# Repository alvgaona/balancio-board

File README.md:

<div align="center">

# balancio-board

**Controller board for the Balancio self-balancing robot.**

</div>

## Overview

The board carries the robot's brains, motor drive and power.

- ESP32 DevKit
- DRV8833 dual motor driver
- MPU-6050 IMU
- 2S battery protection
- Soft-latch power switch, with the power button on the left edge

Rev 1.0 was built by JLCPCB and works. Rev 1.1 replaces its slide switch with the soft latch.

## Layout

- `hw/`: the design, edited in KiCad 10. This is the source of truth.
  - `balancio.kicad_sch`, `balancio.kicad_pcb`: schematic and board.
  - `lib/`: the board's own symbols, footprints and the 3D models KiCad doesn't ship (`balancio.3dshapes/`).
- `scripts/build.sh`: checks the design and writes everything to `build/`.

## Build

You need KiCad 10. FreeCAD is needed only after you edit a model in `hw/lib/balancio.3dshapes/`.

```sh
scripts/build.sh   # or: pixi run build
```

It runs ERC and DRC with schematic parity, and stops on any error before it exports anything.

CI runs the same build in KiCad's Docker image on every push and pull request. The board package is attached to
each run as the `board-package` artifact.

It writes:

- `build/balancio-gerbers.zip`, `build/balancio-bom.csv` and `build/balancio-cpl.csv` for JLCPCB;
- `build/balancio-schematic.pdf`;
- `build/balancio.glb`, the assembled board in 3D, for Blender;
- `build/balancio-rev<rev>.zip`, the board package: all of the above plus the KiCad files, for descent.

## Viewing the board

Open `build/balancio-rev<rev>.zip` in [descent](https://github.com/alvgaona/descent): the 3D model, schematic,
PCB, BOM and every file, in the browser.

descent shows a part as metal when its colour is one of the metals of KiCad's standard 3D models, so our own
models (the DevKit's `.FCStd`) paint metal with those: `#d2d1c7` (metal grey pins) and `#dbbc7e` (gold pins).

`scripts/package.py` writes the package; its docstring describes the format.

## Development

The dev tools (lefthook, commitlint, git-cliff) come from [pixi](https://pixi.sh). Install the git hook once:

```sh
pixi run hooks
```

Commit messages follow [Conventional Commits](https://www.conventionalcommits.org); the `commit-msg` hook checks
them with commitlint.

## Releases

Each board revision is tagged `rev-<rev>`, matching the `rev` in the schematic and PCB title blocks. Pushing the
tag runs the release workflow: it checks the tag against the title blocks, builds the board, and publishes a
GitHub release with the board package, Gerbers, BOM, CPL and schematic PDF. The notes come from git-cliff.
To release a tag that already exists, run the release workflow by hand from the Actions tab and give it the tag.

```sh
pixi run changelog   # write CHANGELOG.md from the commits
```

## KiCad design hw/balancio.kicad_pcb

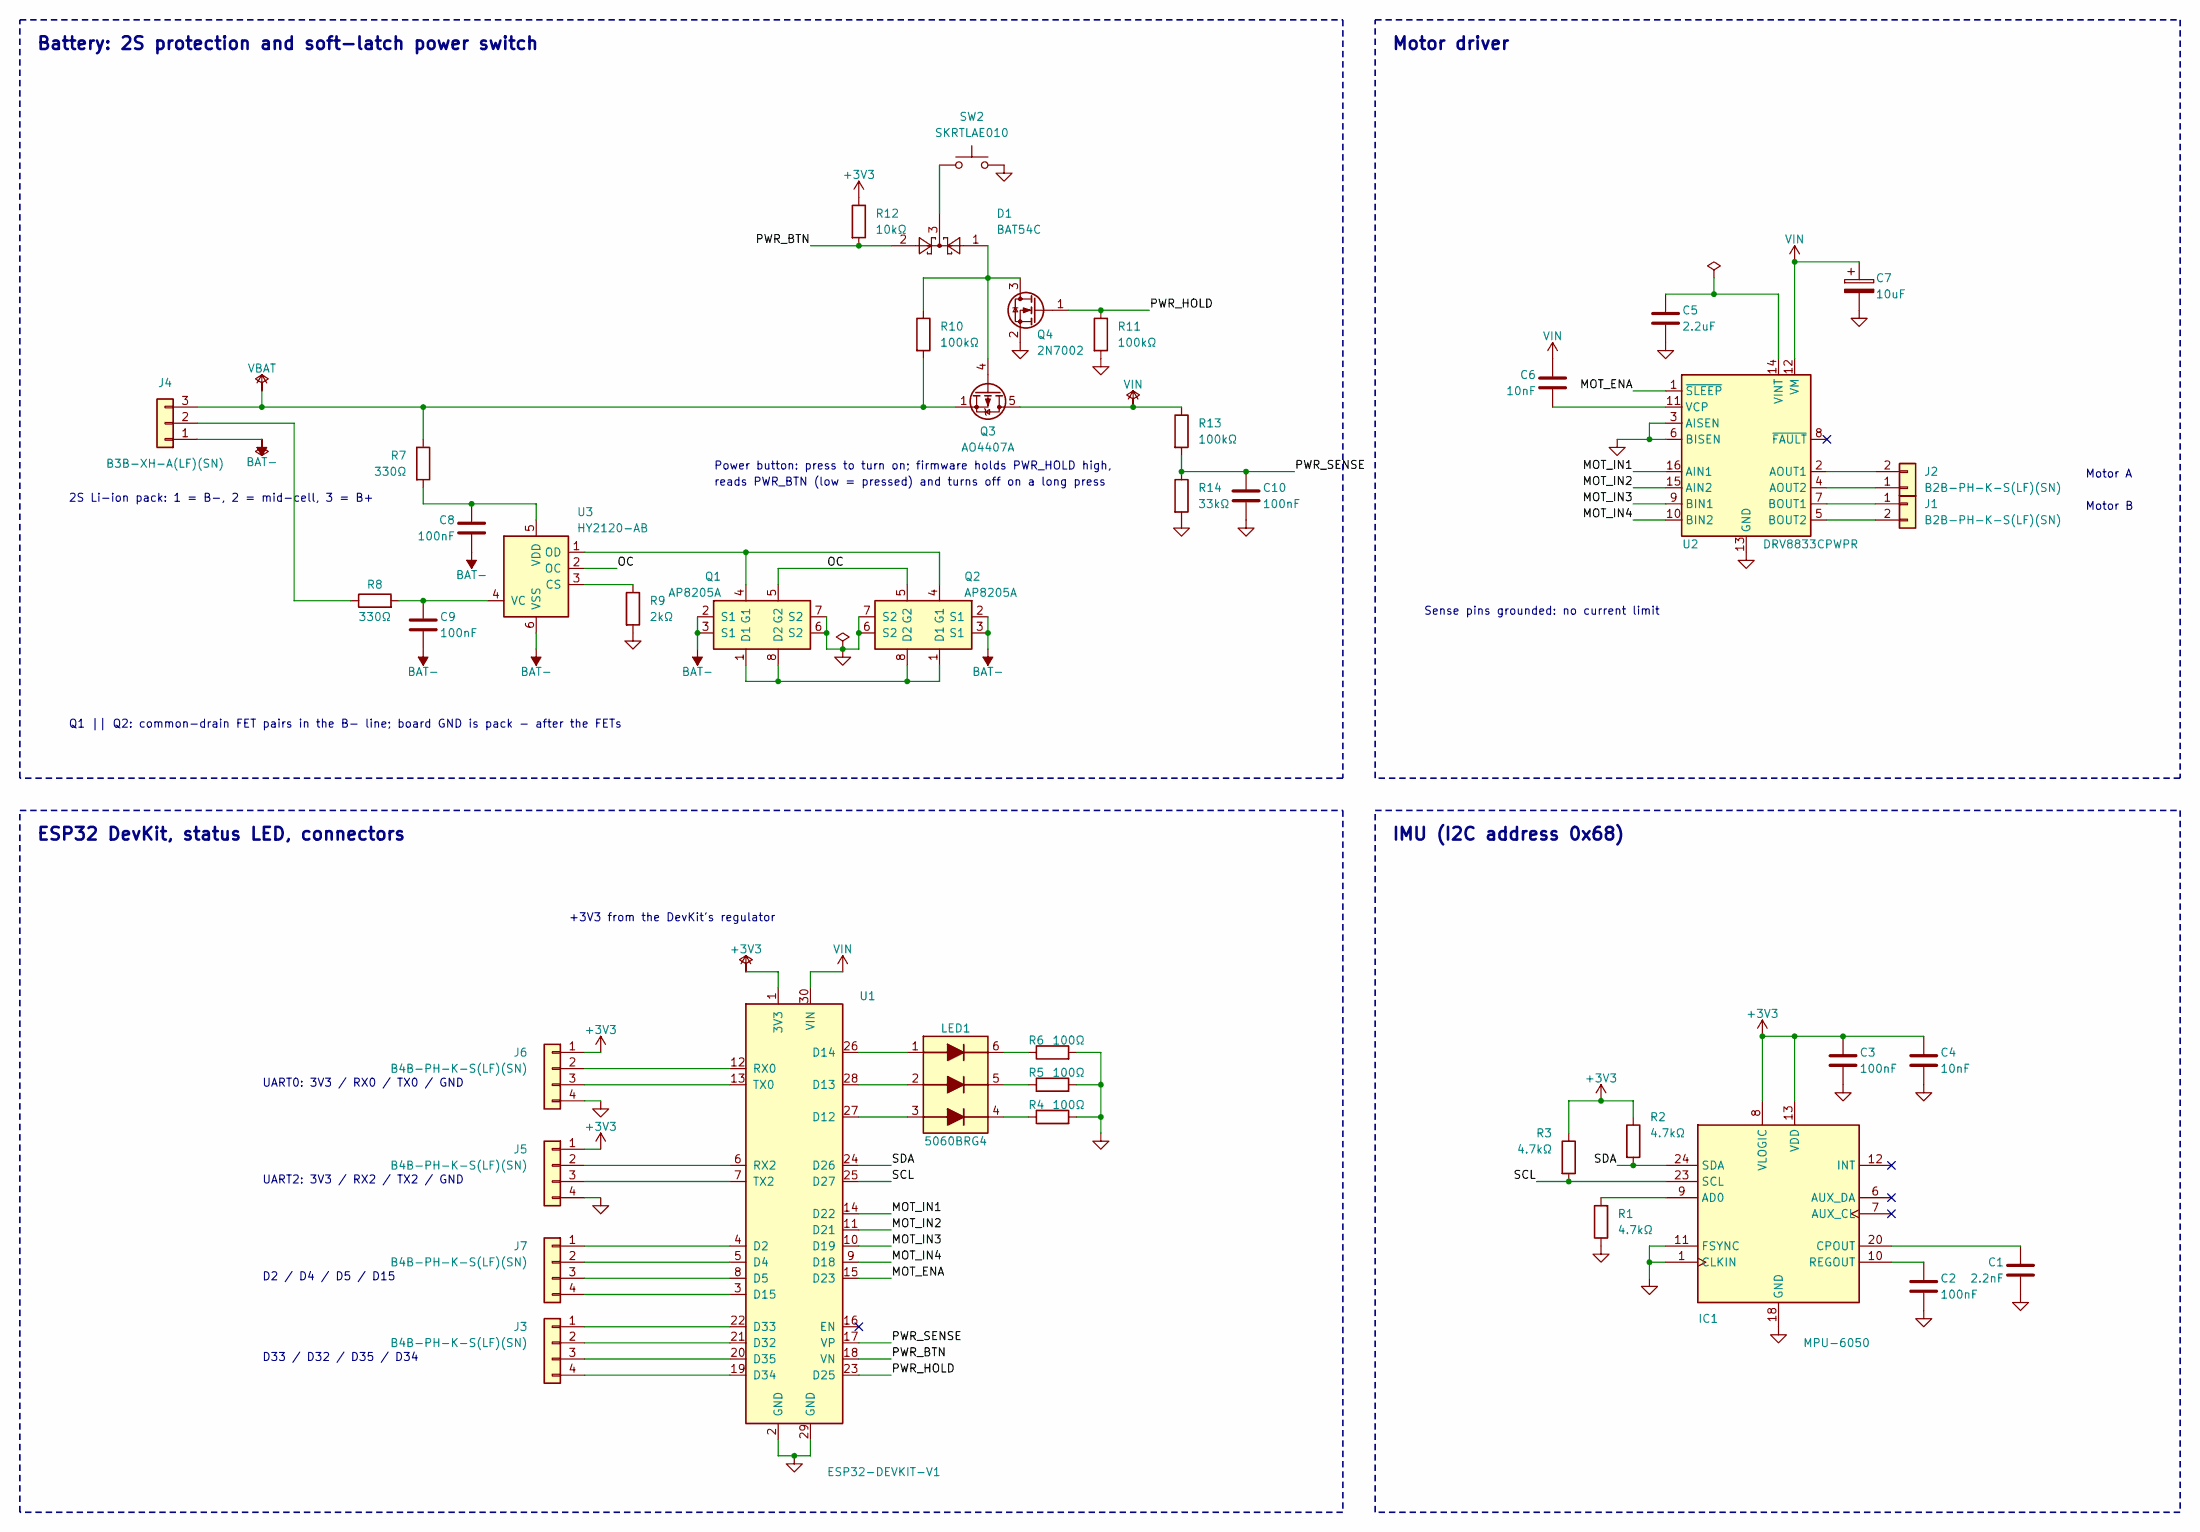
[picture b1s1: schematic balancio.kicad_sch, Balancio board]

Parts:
C1: 2.2nF; C_0805_2012Metric; LCSC C28260
C2, C3, C8, C9, C10: 100nF; C_0805_2012Metric; LCSC C49678
C4, C6: 10nF; C_0805_2012Metric; LCSC C1710
C5: 2.2uF; C_0805_2012Metric; LCSC C377773
C7: 10uF; CP_EIA-3528-21_Kemet-B; MPN CA45-B-25V-10uF-M; LCSC C140404
D1: BAT54C; SOT-23; MPN BAT54C,215; LCSC C37704
IC1: MPU-6050; QFN-24-1EP_4x4mm_P0.5mm; MPN MPU-6050; LCSC C24112
J1, J2: B2B-PH-K-S(LF)(SN); JST_PH_B2B-PH-K_1x02_P2.00mm_Vertical; MPN B2B-PH-K-S(LF)(SN); LCSC C131337
J3, J5, J6, J7: B4B-PH-K-S(LF)(SN); JST_PH_B4B-PH-K_1x04_P2.00mm_Vertical; MPN B4B-PH-K-S(LF)(SN); LCSC C131334
J4: B3B-XH-A(LF)(SN); JST_XH_B3B-XH-A_1x03_P2.50mm_Vertical; MPN B3B-XH-A(LF)(SN); LCSC C144394
LED1: 5060BRG4; LED_RGB_5050-6; MPN 5060BRG4
Q1, Q2: AP8205A; TSSOP-8_4.4x3mm_P0.65mm; MPN AP8205A; LCSC C360341
Q3: AO4407A; SOIC-8_3.9x4.9mm_P1.27mm; MPN AO4407A; LCSC C16072
Q4: 2N7002; SOT-23; MPN 2N7002; LCSC C8545
R1, R2, R3: 4.7kΩ; R_0805_2012Metric; LCSC C17673
R4, R5, R6: 100Ω; R_0805_2012Metric; LCSC C17408
R7, R8: 330Ω; R_0805_2012Metric; LCSC C17630
R9: 2kΩ; R_0805_2012Metric; LCSC C17604
R10, R11, R13: 100kΩ; R_0805_2012Metric; LCSC C149504
R12: 10kΩ; R_0805_2012Metric; LCSC C17414
R14: 33kΩ; R_0805_2012Metric; LCSC C17633
SW2: SKRTLAE010; SW_Push_1P1T-MP_NO_Horizontal_Alps_SKRTLAE010; MPN SKRTLAE010; LCSC C110293
U1: ESP32-DEVKIT-V1; MPN ESP32-DEVKIT-V1
U2: DRV8833CPWPR; TSSOP-16-1EP_4.4x5mm_P0.65mm; MPN DRV8833CPWPR; LCSC C191171
U3: HY2120-AB; SOT-23-6; MPN HY2120-AB; LCSC C168776

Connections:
+3V3: C3.1, C4.1, IC1.8 (VLOGIC), IC1.13 (VDD), J5.1, J6.1, R2.1, R3.1, R12.1, U1.1 (3V3)
/MOT_ENA: U1.15 (D23), U2.1 (~SLEEP)
/MOT_IN1: U1.14 (D22), U2.16 (AIN1)
/MOT_IN2: U1.11 (D21), U2.15 (AIN2)
/MOT_IN3: U1.10 (D19), U2.9 (BIN1)
/MOT_IN4: U1.9 (D18), U2.10 (BIN2)
/OC: Q1.5 (G2), Q2.5 (G2), U3.2 (OC)
/PWR_BTN: D1.2, R12.2, U1.18 (VN)
/PWR_HOLD: Q4.1 (G), R11.1, U1.23 (D25)
/PWR_SENSE: C10.1, R13.2, R14.1, U1.17 (VP)
/SCL: IC1.23 (SCL), R3.2, U1.25 (D27)
/SDA: IC1.24 (SDA), R2.2, U1.24 (D26)
BAT-: C8.2, C9.2, J4.1, Q1.2 (S1), Q1.3 (S1), Q2.2 (S1), Q2.3 (S1), U3.6 (VSS)
GND: C1.2, C2.2, C3.2, C4.2, C5.2, C7.2, C10.2, IC1.1 (CLKIN), IC1.11 (FSYNC), IC1.18 (GND), J5.4, J6.4, Q1.6 (S2), Q1.7 (S2), Q2.6 (S2), Q2.7 (S2), Q4.2 (S), R1.1, R4.2, R5.2, R6.2, R9.2, R11.2, R14.2, SW2.2, U1.2 (GND), U1.29 (GND), U2.3 (AISEN), U2.6 (BISEN), U2.13 (GND), U2.17 (GND)
unnamed: D1.3, SW2.1
unnamed: IC1.9 (AD0), R1.2
unnamed: C1.1, IC1.20 (CPOUT)
unnamed: C2.1, IC1.10 (REGOUT)
unnamed: J1.1, U2.7 (BOUT1)
unnamed: J1.2, U2.5 (BOUT2)
unnamed: J2.1, U2.4 (AOUT2)
unnamed: J2.2, U2.2 (AOUT1)
unnamed: J3.1, U1.22 (D33)
unnamed: J3.2, U1.21 (D32)
unnamed: J3.3, U1.20 (D35)
unnamed: J3.4, U1.19 (D34)
unnamed: J4.2, R8.1
unnamed: J5.2, U1.6 (RX2)
unnamed: J5.3, U1.7 (TX2)
unnamed: J6.2, U1.12 (RX0)
unnamed: J6.3, U1.13 (TX0)
unnamed: J7.1, U1.4 (D2)
unnamed: J7.2, U1.5 (D4)
unnamed: J7.3, U1.8 (D5)
unnamed: J7.4, U1.3 (D15)
unnamed: LED1.1, U1.26 (D14)
unnamed: LED1.2, U1.28 (D13)
unnamed: LED1.3, U1.27 (D12)
unnamed: LED1.4, R4.1
unnamed: LED1.5, R5.1
unnamed: LED1.6, R6.1
unnamed: Q1.1 (D1), Q1.8 (D2), Q2.1 (D1), Q2.8 (D2)
unnamed: Q1.4 (G1), Q2.4 (G1), U3.1 (OD)
unnamed: D1.1, Q3.4 (G), Q4.3 (D), R10.1
unnamed: C6.1, U2.11 (VCP)
unnamed: C5.1, U2.14 (VINT)
unnamed: R9.1, U3.3 (CS)
unnamed: C9.1, R8.2, U3.4 (VC)
unnamed: C8.1, R7.2, U3.5 (VDD)
VBAT: J4.3, Q3.1 (S), Q3.2 (S), Q3.3 (S), R7.1, R10.2
VIN: C6.2, C7.1, Q3.5 (D), Q3.6 (D), Q3.7 (D), Q3.8 (D), R13.1, U1.30 (VIN), U2.12 (VM)

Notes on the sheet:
2S Li-ion pack: 1 = B-, 2 = mid-cell, 3 = B+
Power button: press to turn on; firmware holds PWR_HOLD high,
reads PWR_BTN (low = pressed) and turns off on a long press
Q1 || Q2: common-drain FET pairs in the B- line; board GND is pack - after the FETs
+3V3 from the DevKit's regulator
UART0: 3V3 / RX0 / TX0 / GND
UART2: 3V3 / RX2 / TX2 / GND
D2 / D4 / D5 / D15
D33 / D32 / D35 / D34
Sense pins grounded: no current limit
Motor A
Motor B
Battery: 2S protection and soft-latch power switch
ESP32 DevKit, status LED, connectors
Motor driver
IMU (I2C address 0x68)

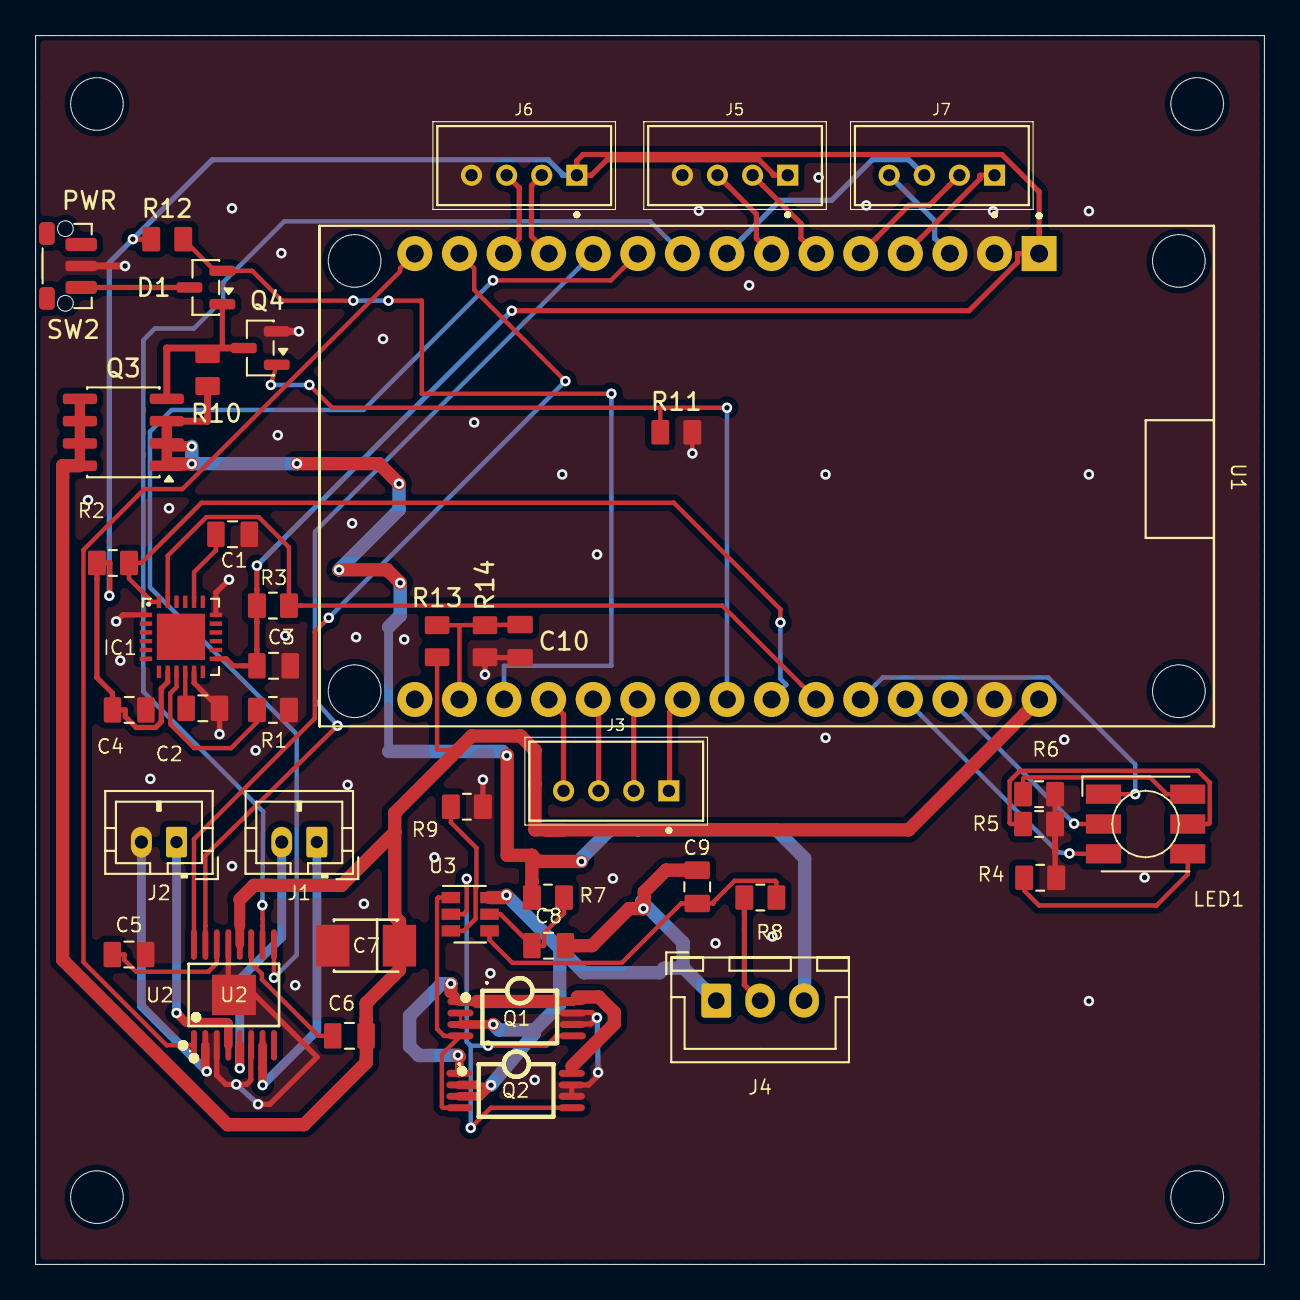
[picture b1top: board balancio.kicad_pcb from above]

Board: 2 copper layers, 70.0 x 70.0 mm, 46 parts (0 on the bottom side), 51 nets.

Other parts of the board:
H1, H2, H3, H4: MountingHole_3mm

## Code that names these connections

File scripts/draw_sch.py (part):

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    q4 = s.place("Q4", 167.64, 27.94, mirror="y", ref_at=(167.64, 31.75, "left"), val_at=(167.64, 34.29, "left"))
    s.power("GND", q4["2"])
    s.w(q4["1"], (185.42, 27.94))
    s.label("PWR_HOLD", (185.42, 27.94))
    r11 = s.place("R11", 177.8, 31.75)
    s.power("GND", r11["2"])
    d1 = s.place("D1", 152.4, 17.78, a=180, ref_at=(161.29, 12.7, "left"), val_at=(161.29, 15.24, "left"))
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    sw = s.place("SW2", 157.48, 5.08, ref_at=(157.48, -2.54, None), val_at=(157.48, 0, None))
    s.power("GND", sw["2"])
    s.w(d1["2"], (132.08, 17.78))
    s.label("PWR_BTN", (132.08, 17.78), 180)
    r12 = s.place("R12", 139.7, 13.97)
    s.power("+3V3", r12["1"])
    s.text("Power button: press to turn on; firmware holds PWR_HOLD high,", 116.84, 53.34)
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    s.w(r13["2"], r14["1"])
    c10 = s.place("C10", 200.66, 57.15)
    s.w(r14["1"], c10["1"], (208.28, 53.34))
    s.label("PWR_SENSE", (208.28, 53.34))
    s.power("GND", r14["2"])
    s.power("GND", c10["2"])

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    s.power("GND", (147.32, row(4) + P))

    # right: signals that leave the block
    for pin, name in (("24", "SDA"), ("25", "SCL"), ("14", "MOT_IN1"), ("11", "MOT_IN2"), ("10", "MOT_IN3"),
                      ("9", "MOT_IN4"), ("15", "MOT_ENA"), ("23", "PWR_HOLD"), ("18", "PWR_BTN"), ("17", "PWR_SENSE")):
        end = (u1[pin][0] + 5.08, u1[pin][1])
        s.w(u1[pin], end)
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def motor_block(s):
    ux, uy = 248.92, 63.5
    u2 = s.place("U2", ux, uy, ref_at=(ux - 10.16, uy + 13.97, "left"), val_at=(ux + 2.54, uy + 13.97, "left"))
    for pin, name in (("1", "MOT_ENA"), ("16", "MOT_IN1"), ("15", "MOT_IN2"), ("9", "MOT_IN3"), ("10", "MOT_IN4")):
        end = (u2[pin][0] - 5.08, u2[pin][1])
        s.w(u2[pin], end)
        s.label(name, end, 180)
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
